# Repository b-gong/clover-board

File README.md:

# clover-board
Important: This is more of a proof of concept for me and needs a lot of improvement.
- No hotswap; and hotswap sockets don't work because the plate is misaligned by fractions of a mm
- Not a big fan of the layout anymore, too big

### 60% + Function Keys with OLED screen and rotary encoder
Who needs the rest of the keyboard xd

### Exposed diodes and Pro Micro for a e s t h e t i c s
Looks sexy

### Namesake of the board (so cute!)

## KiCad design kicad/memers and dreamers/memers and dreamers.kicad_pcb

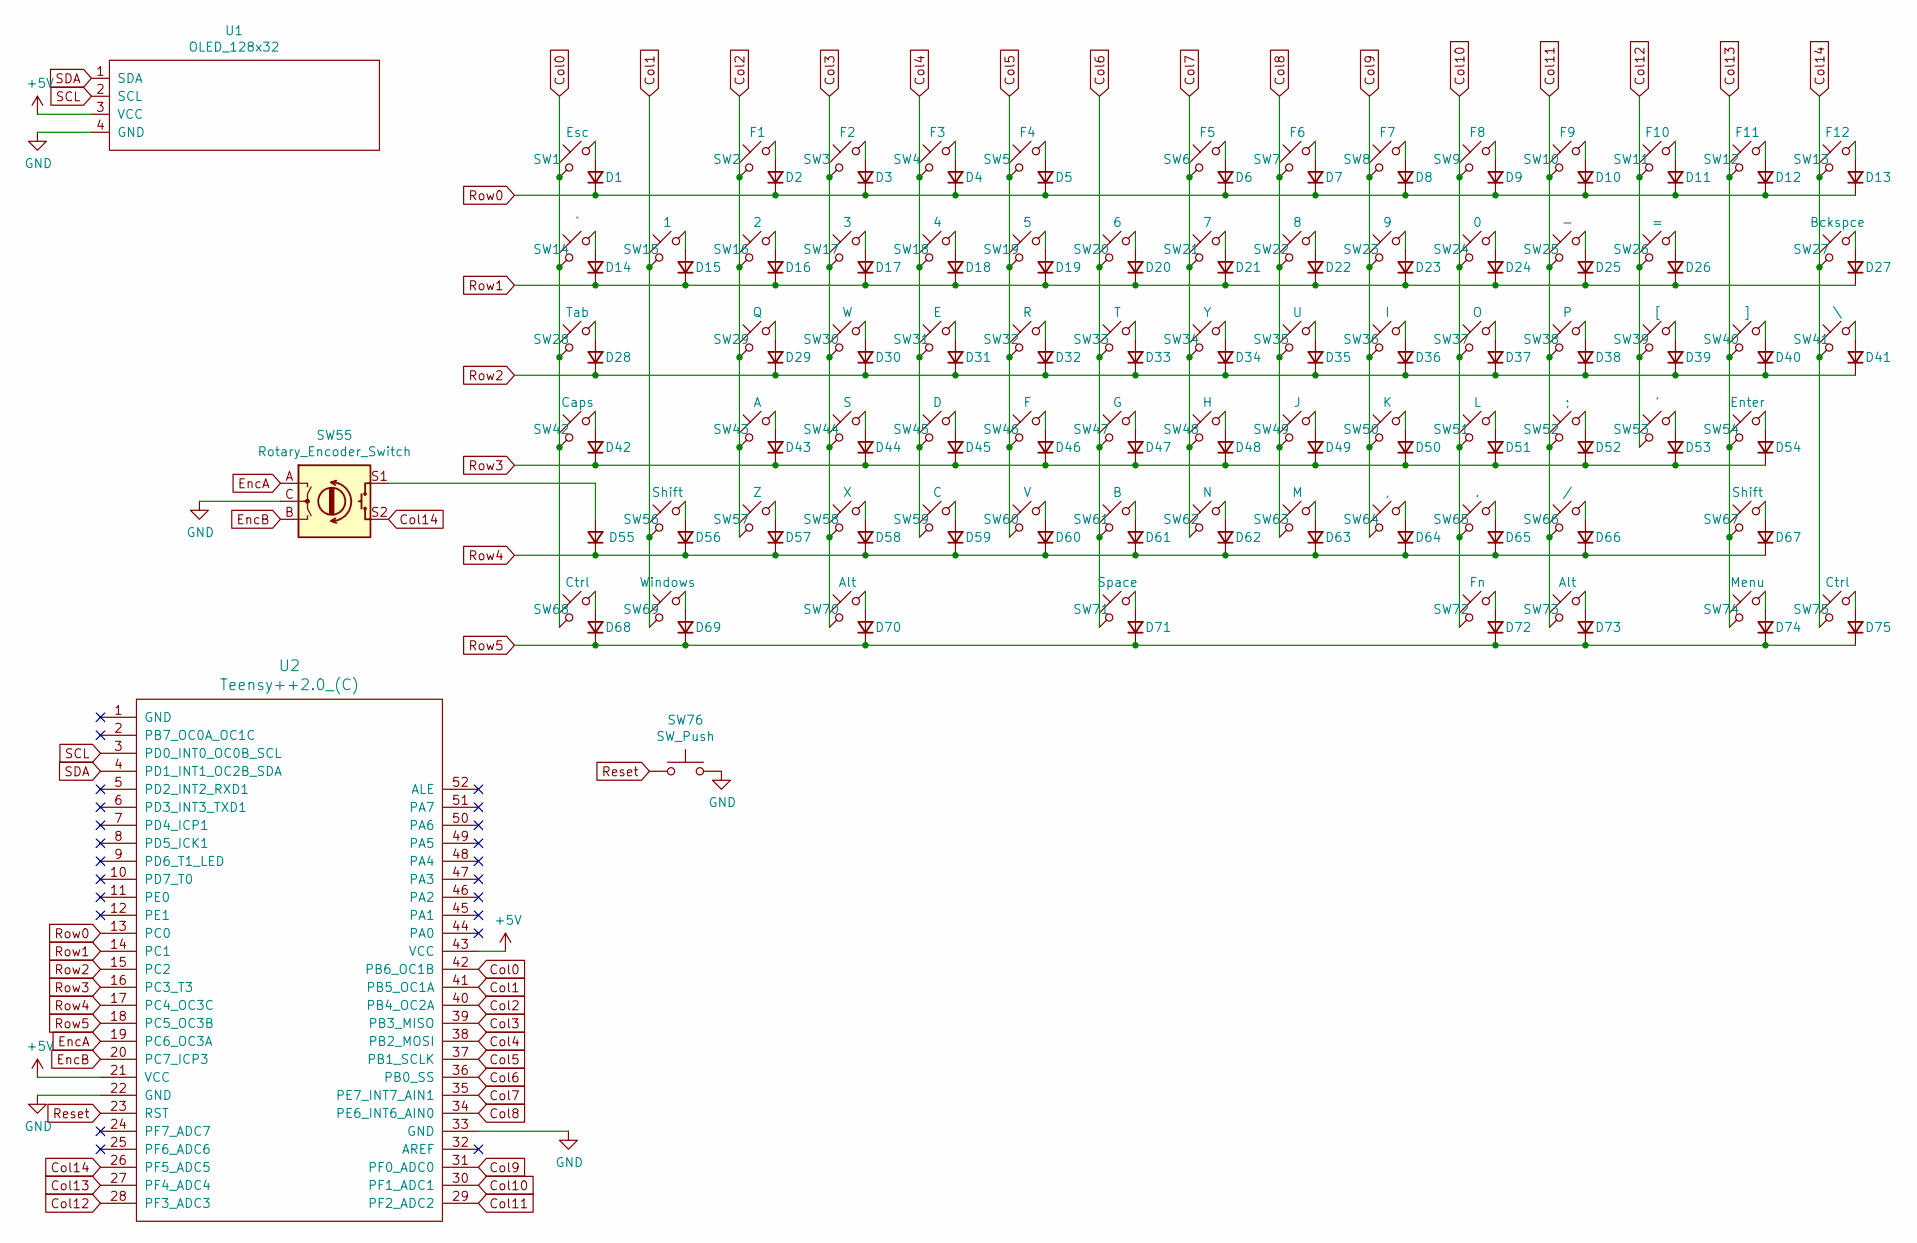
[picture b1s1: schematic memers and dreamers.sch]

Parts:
D1, D2, D3, D4, D5, D6, D7, D8, D9, D10, D11, D12, D13, D14, D15, D16, D17, D18, D19, D20, D21, D22, D23, D24, D25, D26, D27, D28, D29, D30, D31, D32, D33, D34, D35, D36, D37, D38, D39, D40, D41, D42, D43, D44, D45, D46, D47, D48, D49, D50, D51, D52, D53, D54, D55, D56, D57, D58, D59, D60, D61, D62, D63, D64, D65, D66, D67, D68, D69, D70, D71, D72, D73, D74, D75: D_Small; Diode
SW1: Esc; SW_Cherry_MX_1.00u_Plate
SW2: F1; SW_Cherry_MX_1.00u_Plate
SW3: F2; SW_Cherry_MX_1.00u_Plate
SW4: F3; SW_Cherry_MX_1.00u_Plate
SW5: F4; SW_Cherry_MX_1.00u_Plate
SW6: F5; SW_Cherry_MX_1.00u_Plate
SW7: F6; SW_Cherry_MX_1.00u_Plate
SW8: F7; SW_Cherry_MX_1.00u_Plate
SW9: F8; SW_Cherry_MX_1.00u_Plate
SW10: F9; SW_Cherry_MX_1.00u_Plate
SW11: F10; SW_Cherry_MX_1.00u_Plate
SW12: F11; SW_Cherry_MX_1.00u_Plate
SW13: F12; SW_Cherry_MX_1.00u_Plate
SW14: `; SW_Cherry_MX_1.00u_Plate
SW15: 1; SW_Cherry_MX_1.00u_Plate
SW16: 2; SW_Cherry_MX_1.00u_Plate
SW17: 3; SW_Cherry_MX_1.00u_Plate
SW18: 4; SW_Cherry_MX_1.00u_Plate
SW19: 5; SW_Cherry_MX_1.00u_Plate
SW20: 6; SW_Cherry_MX_1.00u_Plate
SW21: 7; SW_Cherry_MX_1.00u_Plate
SW22: 8; SW_Cherry_MX_1.00u_Plate
SW23: 9; SW_Cherry_MX_1.00u_Plate
SW24: 0; SW_Cherry_MX_1.00u_Plate
SW25: -; SW_Cherry_MX_1.00u_Plate
SW26: =; SW_Cherry_MX_1.00u_Plate
SW27: Bckspce; SW_Cherry_MX_2.00u_Plate
SW28: Tab; SW_Cherry_MX_1.50u_Plate
SW29: Q; SW_Cherry_MX_1.00u_Plate
SW30: W; SW_Cherry_MX_1.00u_Plate
SW31: E; SW_Cherry_MX_1.00u_Plate
SW32: R; SW_Cherry_MX_1.00u_Plate
SW33: T; SW_Cherry_MX_1.00u_Plate
SW34: Y; SW_Cherry_MX_1.00u_Plate
SW35: U; SW_Cherry_MX_1.00u_Plate
SW36: I; SW_Cherry_MX_1.00u_Plate
SW37: O; SW_Cherry_MX_1.00u_Plate
SW38: P; SW_Cherry_MX_1.00u_Plate
SW39: [; SW_Cherry_MX_1.00u_Plate
SW40: ]; SW_Cherry_MX_1.00u_Plate
SW41: \\; SW_Cherry_MX_1.50u_Plate
SW42: Caps; SW_Cherry_MX_1.75u_Plate
SW43: A; SW_Cherry_MX_1.00u_Plate
SW44: S; SW_Cherry_MX_1.00u_Plate
SW45: D; SW_Cherry_MX_1.00u_Plate
SW46: F; SW_Cherry_MX_1.00u_Plate
SW47: G; SW_Cherry_MX_1.00u_Plate
SW48: H; SW_Cherry_MX_1.00u_Plate
SW49: J; SW_Cherry_MX_1.00u_Plate
SW50: K; SW_Cherry_MX_1.00u_Plate
SW51: L; SW_Cherry_MX_1.00u_Plate
SW52: ;; SW_Cherry_MX_1.00u_Plate
SW53: '; SW_Cherry_MX_1.00u_Plate
SW54: Enter; SW_Cherry_MX_2.25u_Plate
SW55: Rotary_Encoder_Switch; RotaryEncoder_EC11
SW56: Shift; SW_Cherry_MX_2.25u_Plate
SW57: Z; SW_Cherry_MX_1.00u_Plate
SW58: X; SW_Cherry_MX_1.00u_Plate
SW59: C; SW_Cherry_MX_1.00u_Plate
SW60: V; SW_Cherry_MX_1.00u_Plate
SW61: B; SW_Cherry_MX_1.00u_Plate
SW62: N; SW_Cherry_MX_1.00u_Plate
SW63: M; SW_Cherry_MX_1.00u_Plate
SW64: ,; SW_Cherry_MX_1.00u_Plate
SW65: .; SW_Cherry_MX_1.00u_Plate
SW66: /; SW_Cherry_MX_1.00u_Plate
SW67: Shift; SW_Cherry_MX_2.75u_Plate
SW68, SW75: Ctrl; SW_Cherry_MX_1.25u_Plate
SW69: Windows; SW_Cherry_MX_1.25u_Plate
SW70, SW73: Alt; SW_Cherry_MX_1.25u_Plate
SW71: Space; SW_Cherry_MX_6.25u_Plate
SW72: Fn; SW_Cherry_MX_1.25u_Plate
SW74: Menu; SW_Cherry_MX_1.25u_Plate
SW76: SW_Push; SW_PUSH_6mm
U1: OLED_128x32
U2: Teensy++2.0_(C); Teensy2.0++

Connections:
+5V: U1.3 (VCC), U2.21 (VCC), U2.43 (VCC)
Col0: SW1.1, SW14.1, SW28.1, SW42.1, SW68.1, U2.42 (PB6_OC1B)
Col1: SW15.1, SW56.1, SW69.1, U2.41 (PB5_OC1A)
Col2: SW2.1, SW16.1, SW29.1, SW43.1, SW57.1, U2.40 (PB4_OC2A)
Col3: SW3.1, SW17.1, SW30.1, SW44.1, SW58.1, SW70.1, U2.39 (PB3_MISO)
Col4: SW4.1, SW18.1, SW31.1, SW45.1, SW59.1, U2.38 (PB2_MOSI)
Col5: SW5.1, SW19.1, SW32.1, SW46.1, SW60.1, U2.37 (PB1_SCLK)
Col6: SW20.1, SW33.1, SW47.1, SW61.1, SW71.1, U2.36 (PB0_SS)
Col7: SW6.1, SW21.1, SW34.1, SW48.1, SW62.1, U2.35 (PE7_INT7_AIN1)
Col8: SW7.1, SW22.1, SW35.1, SW49.1, SW63.1, U2.34 (PE6_INT6_AIN0)
Col9: SW8.1, SW23.1, SW36.1, SW50.1, SW64.1, U2.31 (PF0_ADC0)
Col10: SW9.1, SW24.1, SW37.1, SW51.1, SW65.1, SW72.1, U2.30 (PF1_ADC1)
Col11: SW10.1, SW25.1, SW38.1, SW52.1, SW66.1, SW73.1, U2.29 (PF2_ADC2)
Col12: SW11.1, SW26.1, SW39.1, SW53.1, U2.28 (PF3_ADC3)
Col13: SW12.1, SW40.1, SW54.1, SW67.1, SW74.1, U2.27 (PF4_ADC4)
Col14: SW13.1, SW27.1, SW41.1, SW55.S2, SW75.1, U2.26 (PF5_ADC5)
EncA: SW55.A, U2.19 (PC6_OC3A)
EncB: SW55.B, U2.20 (PC7_ICP3)
GND: SW55.C, SW76.2, U1.4 (GND), U2.22 (GND), U2.33 (GND)
unnamed: D1.2 (A), SW1.2
unnamed: D2.2 (A), SW2.2
unnamed: D3.2 (A), SW3.2
unnamed: D4.2 (A), SW4.2
unnamed: D5.2 (A), SW5.2
unnamed: D6.2 (A), SW6.2
unnamed: D7.2 (A), SW7.2
unnamed: D8.2 (A), SW8.2
unnamed: D9.2 (A), SW9.2
unnamed: D10.2 (A), SW10.2
unnamed: D11.2 (A), SW11.2
unnamed: D12.2 (A), SW12.2
unnamed: D13.2 (A), SW13.2
unnamed: D14.2 (A), SW14.2
unnamed: D15.2 (A), SW15.2
unnamed: D16.2 (A), SW16.2
unnamed: D17.2 (A), SW17.2
unnamed: D18.2 (A), SW18.2
unnamed: D19.2 (A), SW19.2
unnamed: D20.2 (A), SW20.2
unnamed: D21.2 (A), SW21.2
unnamed: D22.2 (A), SW22.2
unnamed: D23.2 (A), SW23.2
unnamed: D24.2 (A), SW24.2
unnamed: D25.2 (A), SW25.2
unnamed: D26.2 (A), SW26.2
unnamed: D27.2 (A), SW27.2
unnamed: D28.2 (A), SW28.2
unnamed: D29.2 (A), SW29.2
unnamed: D30.2 (A), SW30.2
unnamed: D31.2 (A), SW31.2
unnamed: D32.2 (A), SW32.2
unnamed: D33.2 (A), SW33.2
unnamed: D34.2 (A), SW34.2
unnamed: D35.2 (A), SW35.2
unnamed: D36.2 (A), SW36.2
unnamed: D37.2 (A), SW37.2
unnamed: D38.2 (A), SW38.2
unnamed: D39.2 (A), SW39.2
unnamed: D40.2 (A), SW40.2
unnamed: D41.2 (A), SW41.2
unnamed: D42.2 (A), SW42.2
unnamed: D43.2 (A), SW43.2
unnamed: D44.2 (A), SW44.2
unnamed: D45.2 (A), SW45.2
unnamed: D46.2 (A), SW46.2
unnamed: D47.2 (A), SW47.2
unnamed: D48.2 (A), SW48.2
unnamed: D49.2 (A), SW49.2
unnamed: D50.2 (A), SW50.2
unnamed: D51.2 (A), SW51.2
unnamed: D52.2 (A), SW52.2
unnamed: D53.2 (A), SW53.2
unnamed: D54.2 (A), SW54.2
unnamed: D55.2 (A), SW55.S1
unnamed: D56.2 (A), SW56.2
unnamed: D57.2 (A), SW57.2
unnamed: D58.2 (A), SW58.2
unnamed: D59.2 (A), SW59.2
unnamed: D60.2 (A), SW60.2
unnamed: D61.2 (A), SW61.2
unnamed: D62.2 (A), SW62.2
unnamed: D63.2 (A), SW63.2
unnamed: D64.2 (A), SW64.2
unnamed: D65.2 (A), SW65.2
unnamed: D66.2 (A), SW66.2
unnamed: D67.2 (A), SW67.2
unnamed: D68.2 (A), SW68.2
unnamed: D69.2 (A), SW69.2
unnamed: D70.2 (A), SW70.2
unnamed: D71.2 (A), SW71.2
unnamed: D72.2 (A), SW72.2
unnamed: D73.2 (A), SW73.2
unnamed: D74.2 (A), SW74.2
unnamed: D75.2 (A), SW75.2
Reset: SW76.1, U2.23 (RST)
Row0: D1.1 (K), D2.1 (K), D3.1 (K), D4.1 (K), D5.1 (K), D6.1 (K), D7.1 (K), D8.1 (K), D9.1 (K), D10.1 (K), D11.1 (K), D12.1 (K), D13.1 (K), U2.13 (PC0)
Row1: D14.1 (K), D15.1 (K), D16.1 (K), D17.1 (K), D18.1 (K), D19.1 (K), D20.1 (K), D21.1 (K), D22.1 (K), D23.1 (K), D24.1 (K), D25.1 (K), D26.1 (K), D27.1 (K), U2.14 (PC1)
Row2: D28.1 (K), D29.1 (K), D30.1 (K), D31.1 (K), D32.1 (K), D33.1 (K), D34.1 (K), D35.1 (K), D36.1 (K), D37.1 (K), D38.1 (K), D39.1 (K), D40.1 (K), D41.1 (K), U2.15 (PC2)
Row3: D42.1 (K), D43.1 (K), D44.1 (K), D45.1 (K), D46.1 (K), D47.1 (K), D48.1 (K), D49.1 (K), D50.1 (K), D51.1 (K), D52.1 (K), D53.1 (K), D54.1 (K), U2.16 (PC3_T3)
Row4: D55.1 (K), D56.1 (K), D57.1 (K), D58.1 (K), D59.1 (K), D60.1 (K), D61.1 (K), D62.1 (K), D63.1 (K), D64.1 (K), D65.1 (K), D66.1 (K), D67.1 (K), U2.17 (PC4_OC3C)
Row5: D68.1 (K), D69.1 (K), D70.1 (K), D71.1 (K), D72.1 (K), D73.1 (K), D74.1 (K), D75.1 (K), U2.18 (PC5_OC3B)
SCL: U1.2 (SCL), U2.3 (PD0_INT0_OC0B_SCL)
SDA: U1.1 (SDA), U2.4 (PD1_INT1_OC2B_SDA)

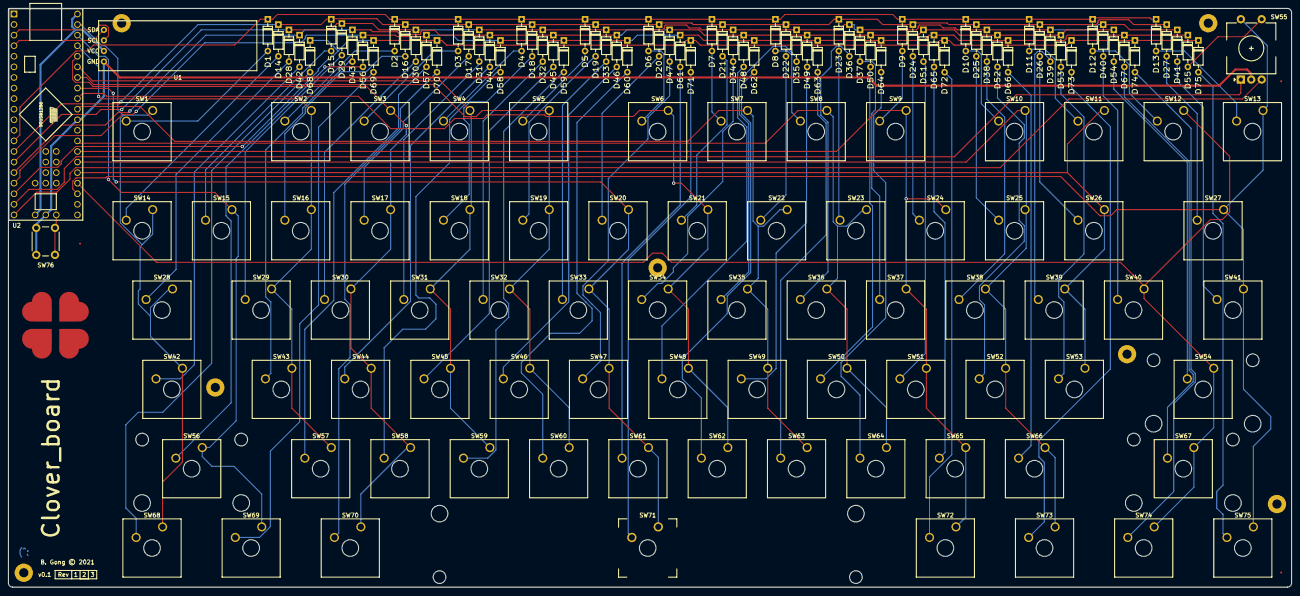
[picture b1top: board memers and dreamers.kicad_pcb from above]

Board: 2 copper layers, 308.2 x 139.0 mm, 153 parts (0 on the bottom side), 103 nets.

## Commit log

2021-01-03 Uploaded files
2021-01-03 added 3d model of the board
2021-01-03 Added picture of namesake
2021-01-03 added clover pic to readme and updated formatting
2021-01-03 update alt text
2021-01-03 update bottom
2022-09-13 add irl pics
2022-09-13 rotate image
2022-09-13 add screen rotated
2022-09-13 add real life pics
2022-09-13 render
2022-09-14 added firmware and move kicad stuff to its own file

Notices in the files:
kicad/memers and dreamers/memers and dreamers.kicad_pcb:
B. Gong © 2021
